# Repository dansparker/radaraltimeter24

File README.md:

# radaraltimeter24

FMCW-Radar-Höhenmesser (Radar Altimeter) für Flugzeuge mit 24-GHz-Radarmodul
(**RFbeam K-LC1a** oder **InnoSenT IVS-465**) und **STM32F405RGT6** (Rev. A) bzw.
**STM32F446** auf dem WeAct-Core-Board (Rev. B, [Schaltplan](hardware/rev_b_f446/README.md)).
Ausgabe ~61 Hz über **UART** und **CAN**. Kurze Dreieckrampen (1,17 ms), viele Rampen
gemittelt und die **Vorderkante** des Bodenechos ausgewertet: Der Boden ist aus dem Flugzeug
kein Punktziel, sondern wegen Keule und Fluggeschwindigkeit ein breiter Hügel im Spektrum.

Reichweite mit dem K-LC1a im Simulator (Empfindlichkeit nach Datenblatt, 30 m/s): über Wiese
bis etwa 100 m, über Asphalt/Wasser bis 250 m, kleinste Höhe etwa 4 m. Einzelheiten:
[hardware/rev_b_f446/README.md](hardware/rev_b_f446/README.md#mögliche-reichweite).

## Aufbau

```
lib/rdsp/            portable Radar-DSP-Bibliothek (C99, ohne malloc, wiederverwendbar)
firmware/app/        Höhenmesser-Pipeline, Konfiguration, Protokolle (hardwareunabhängig)
firmware/bsp/        STM32F405 (Rev. A) / F446 (Rev. B): Startup, Takt, Frontend (DAC/ADC/DMA), UART, CAN, Flash, IWDG
firmware/src/        main.c, Kommandozeile
test/                Radar-Simulator mit Bodenmodell + Unit-/End-to-End-Tests, Reichweitenauswertung
docs/                Signalverarbeitung, Hardware, Review/Schwachstellen
hardware/rev_b_f446/ Schaltplan Rev. B (STM32F446, TLV9064), Reichweitenabschätzung
```

## Signalverarbeitung (Kurzfassung)

Dreieck-FMCW (steigende und fallende Rampe abwechselnd, je 1,17 ms; ein Messzyklus = 7 Paare):

| Schritt | Modul | Zweck |
|---|---|---|
| 0 | `rdsp_agc` | Verstärkungsregelung (4 Stufen), ignoriert einzelne Störpulse |
| 1 | `rdsp_frame` | ADC → float, Statistik, Clipping, DC-/Trendabzug |
| 2 | `rdsp_window` | Hann-Fenster über 256 Samples, Nullauffüllung |
| 3 | `rdsp_fft` | reelle FFT 512 Punkte |
| 3a | `rdsp_clutter_update` | laufender Abzug fester Echos (Leckage, Fahrwerk), kohärenzgewichtet |
| 4 | `rdsp_spectrum` | Leistungsdichte, robuste Mittelung über Rampen (τ 40–250 ms) |
| 5 | `rdsp_edge` | Vorderkante des Bodenechos (nur rückwärts schauendes Rauschfenster) |
| 6 | `rdsp_fmcw` | Auf/Ab-Kombination → dopplerfreie Entfernung + Geschwindigkeit |
| 7 | `rdsp_track` | α-β-Tracker mit Gating, Coasting, Wiederaufnahme |

Details, Begründungen und weitere Diagramme: [docs/signal_chain.md](docs/signal_chain.md).

## Bauen

Firmware (arm-none-eabi-gcc, z. B. aus STM32CubeIDE):

```bash
sh tools/fetch_cmsis.sh
```

```bash
make -C firmware              # Rev. B (STM32F446), Standard
make -C firmware BOARD=reva   # Rev. A (STM32F405)
```

Ergebnis: `firmware/build/<board>/radar_altimeter.{elf,bin,hex}`. Alternativ kann `CMSIS=<pfad>` auf
einen vorhandenen CubeIDE-`Drivers/CMSIS`-Ordner zeigen. Der Code nutzt keine HAL, nur
CMSIS-Registerdefinitionen.

Host-Tests (gcc/clang):

```bash
make -C test
```

Reichweite/Genauigkeit gegen das Bodenmodell (einige Minuten):

```bash
make -C test range
```

## Inbetriebnahme

1. Firmware flashen, UART 115200 8N1 öffnen → `$RALT`-Zeilen.
2. `module klc1a` bzw. `module ivs465`, dann `info`.
3. **Kalibrierung** (Frequenzhub der Module unbekannt!): `bg off`, Radar auf einen Reflektor
   (Winkelreflektor, Metallplatte) in bekanntem Abstand richten, `cal1 <m>`, Abstand ändern
   (≥ 2 m, besser ≥ 10 m), `cal2 <m>`, dann `bg on`, `save`.
4. Optional, eingebaut am Flugzeug: `zero 0` (Anzeige = 0 auf dem Boden), `save`.
5. Laufender Hintergrundabzug (`bg on`, Standard) entfernt im Flug feste Echos (Leckage, Radom,
   Fahrwerk). Bei Bodentests mit ruhendem Ziel `bg off`, vor dem Flug wieder `bg on`, `save`.

Alle Kommandos: `help`. Siehe [docs/hardware.md](docs/hardware.md) und die vollständige
**[Checkliste zur Inbetriebnahme](docs/inbetriebnahme.md)**.

## Ausgabe

UART (NMEA-ähnlich, XOR-Prüfsumme):

```
$RALT,<seq>,<höhe_m>,<vs_m/s>,<snr_dB>,<gain>,<status_hex>*CS
$RDBG,<seq>,<roh_m>,<kante_steigend_Hz>,<kante_fallend_Hz>,<f_R_Hz>,<track>,<tau_ms>*CS   (out 2)
```

Höhe und Geschwindigkeit sind leer, wenn ungültig. CAN (Standard-ID `0x3A0`, 500 kbit/s):

| ID | Bytes |
|---|---|
| 0x3A0 | int32 Höhe [mm], int16 Steigrate [cm/s], uint8 Status (Low-Byte), uint8 Zähler(0-3) \| Gain(4-5) \| degraded(6) \| busy(7) |
| 0x3A1 | uint16 Status, uint8 SNR [dB], uint8 Track-Zustand, uint32 seq (jede 8. Messung) |

Statusbits: `0x0001` gültig, `0x0002` Coasting, `0x0004` kein Ziel, `0x0008` Clipping,
`0x0010` Hardwarefehler, `0x0020` nicht kalibriert, `0x0040` Frame-Überlauf,
`0x0080` degradiert (nur eine Rampenrichtung oder Kante nahe DC), `0x0100` Kalibrierung läuft,
`0x0200` Gain-Wechsel, `0x0400` Taktausfall (läuft auf HSI).
Das letzte Feld von `$RDBG` ist die aktuelle Mittelungszeit in ms.

## Status / Einschränkungen

Die Firmware ist im Simulator getestet und kompiliert, **aber noch nicht auf der Hardware
erprobt**. Bekannte Grenze: Bei hoher Fluggeschwindigkeit misst sie systematisch zu niedrig
(30 m/s: ≈ 0,5 m, 60 m/s: 1–2 m). Offene Punkte und gefundene Schwachstellen: [docs/review.md](docs/review.md).
Nicht als zertifiziertes Avionik-Gerät gedacht.

## Lizenz

MIT, siehe [LICENSE](LICENSE).

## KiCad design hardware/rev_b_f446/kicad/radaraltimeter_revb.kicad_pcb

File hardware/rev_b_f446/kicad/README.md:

# KiCad-Projekt Rev. B (KiCad 9)

Inhaltlich gleich wie [`../schaltplan.svg`](../schaltplan.svg). Der SVG-Plan ist die lesbare
Zeichnung. Der KiCad-Schaltplan ist netzlistenartig aufgebaut: Jeder Pin hat ein Netzlabel,
geordnet nach den sechs Blöcken des SVG-Plans.

| Datei | Inhalt |
|---|---|
| `radaraltimeter_revb.kicad_pro / .kicad_sch / .kicad_pcb` | Projekt, Schaltplan, Platine |
| `radar_revb.kicad_sym`, `radar_revb.pretty/` | Projektbibliothek: WeAct-Board, K-LC1a, TS3A5017 (TSSOP), PESD3V3S2UT |
| `radaraltimeter_revb_schaltplan.pdf`, `_platine.pdf`, `_bestueckung.pdf` | Export zum Ansehen ohne KiCad (Bestückungsplan mit allen Referenzen) |
| `generator/` | Skripte, aus denen alles erzeugt wurde (`design.py` = Netzliste) |

## Stand

- **Schaltplan:** ERC 0 Fehler, 0 Warnungen.
- **Platine:**
  - 4 Lagen, 86 × 64 mm, 4 × M3 an GND.
  - GND-Fläche auf In1 (durchgehend) und B.Cu; jedes SMD-GND-Pad hat ein eigenes Via auf In1.
  - ZF-Kette und VCO-Ansteuerung von Hand verankert (`generator/place_if.py`): U1 um 180° gedreht,
    die Stufen 1 und 2 zeigen zum Modulpin. C21 sitzt direkt zwischen Modulpin 3 und dem U1-Eingang,
    U7 mit 1D neben U1 Pin 6. Die übrigen Teile setzt das Skript in Signalrichtung auf den nächsten
    freien Platz, Abblockkondensatoren an ihren Versorgungspin, R32/C27 an PC4.
  - Restliche Gruppen gepackt, Zweipoler per Tausch/Drehung auf kurze Netze optimiert.
  - **Mit Freerouting geroutet** (F.Cu 1,2 m, In2 0,23 m, B.Cu 0,15 m; In1 bleibt ungeteilte
    Masselage). DRC mit Schaltplan-Parität: **0 Verstöße**, 0 offene Verbindungen.
  - Analoge Netze, alle auf F.Cu über der Masselage und ohne Via: IF_RAW 8 mm, IF_AC 6 mm,
    IF_FB1 6 mm, IF1 4 mm, IF_HP 13 mm, IF_FB2 12 mm, ADC_IF 5 mm, VCO_DRV 10 mm.
    VCO_TUNE 24 mm mit einem Via. Die langen Wege tragen niederohmige Signale
    (AA1/AA2-Ausgänge, DAC, Steuerleitungen).
  - Bestückungsdruck aufgeräumt (`generator/silk.py`): Referenzen auf freien Plätzen, weg von
    Pads, Vias, anderem Druck und der Kante; bei ICs auf dem Gehäuse. Wo im dichten ZF-Feld kein
    Platz ist (21 Kleinteile, TP1, D6), steht die Referenz nur auf F.Fab, also im Bestückungsplan
    `radaraltimeter_revb_bestueckung.pdf`. Library-Footprints bleiben unverändert.
  - Vor der Bestellung trotzdem in KiCad ansehen: Leiterbahnen glätten, Kabelaustritt J1 prüfen.
- Netzklasse `Power` (0,5 mm) für VIN*, BUCK_SW, V_PRE*, 5V_* und GND.

Anordnung (oben gesehen):
- WeAct-Board links auf Buchsenleisten 2 × 2×15, um 180° gedreht. USB-C liegt an der Oberkante, die Analog-Leiste (PA4, PC4, PC5, PB0, PB1) zeigt zur Mitte.
- K-LC1a **auf der Unterseite**, Antenne nach unten. Die Pins stehen rechts, die ZF-Kette liegt darüber auf der Oberseite.
- Schaltregler und Stecker J1 liegen unten, möglichst weit weg von der ZF-Kette.

## Neu erzeugen

Änderungen an Bauteilen oder Netzen in `generator/design.py` machen, dann:

```bash
python generator/mklib.py && python generator/gen_sch.py
"D:/Program Files/KiCad/9.0/bin/python.exe" generator/gen_pcb.py
"D:/Program Files/KiCad/9.0/bin/python.exe" generator/route.py
"D:/Program Files/KiCad/9.0/bin/python.exe" generator/silk.py
```

`gen_pcb.py` und `route.py` brauchen das Python von KiCad (Modul `pcbnew`), `route.py` zusätzlich
Java und Freerouting (Pfad über `FREEROUTING`, Standard `~/AppData/Local/freerouting/freerouting-1.9.0.jar`).
Der K-LC1a hat einen eigenen Unterseiten-Footprint statt eines gespiegelten Teils, weil der
DSN-Export von KiCad 9 gespiegelten Durchsteck-Pads die Innenlagen nimmt. **Achtung:** Neu erzeugen
überschreibt die Platine samt Routing. Sobald in KiCad geroutet wird, Änderungen nur noch in
KiCad machen (Schaltplan → Platine mit F8).

## Vor dem Routing/Bestellen prüfen

1. **WeAct-Pinfolge:** Die Pinfolge stammt aus dem Board-Shape-PDF V1.0 von WeAct. Pro Leiste gilt: linke Beschriftung = äußere Reihe (links) bzw. innere Reihe (rechts).
   - Genutzt werden PA2, PA3, PA4, PC4, PC5, PB0, PB1, PB8, PB9, PB12, PB13, PC6, PC7, 5V, 3V3 und GND.
   - Mit Durchgangsprüfer am echten Board (V1.1) nachmessen, vor allem 5V/GND unten rechts und 3V3/GND unten links. Die Reihen L12 bis L14 innen sind unbeschriftet und bleiben offen.
2. **K-LC1a:**
   - Laut Datenblatt Fig. 3 sind die Pins 2,54 mm, Pin 1 sitzt 7,42 mm von der Kante.
   - Der Abstand der Pinreihe zum Modulrand (1,45 mm) ist aus der Zeichnung geschätzt.
   - Bohrung 1,0 mm für 0,64-mm-Pins. Abstand Platine zu Modul so wählen, dass nichts auf der Unterseite das Gehäuse berührt.
3. **TS3A5017 TSSOP-16:** Pinbelegung nach TI SCDS188G (1 = 1EN, 2 = IN2, 7 = 1D, 14 = IN1, 15 = 2EN, 16 = V+). Die Kanalzuordnung (S1 = 55,5-fach … S4 = 1-fach) muss zur Tabelle der Firmware passen.
4. **Footprints der Fremdteile:**
   - J1 ist JST GH, Kabelaustritt prüfen.
   - L1/L2 als Bourns SRN4018 oder Gleichwertiges (L2: Sättigungsstrom ≥ 1 A).
   - C21 ist Folie im Format 1812, eine passende Bauform suchen.
5. **Layout-Regeln** (siehe Hinweise im SVG-Plan):
   - Massefläche nicht auftrennen.
   - IF_RAW → C21 → U1A kurz halten.
   - BUCK_SW-Schleife (U3, D4, L2, C2) klein halten und weit weg von der ZF.
   - ADC_IF mit R32/C27 nahe an PC4 führen.

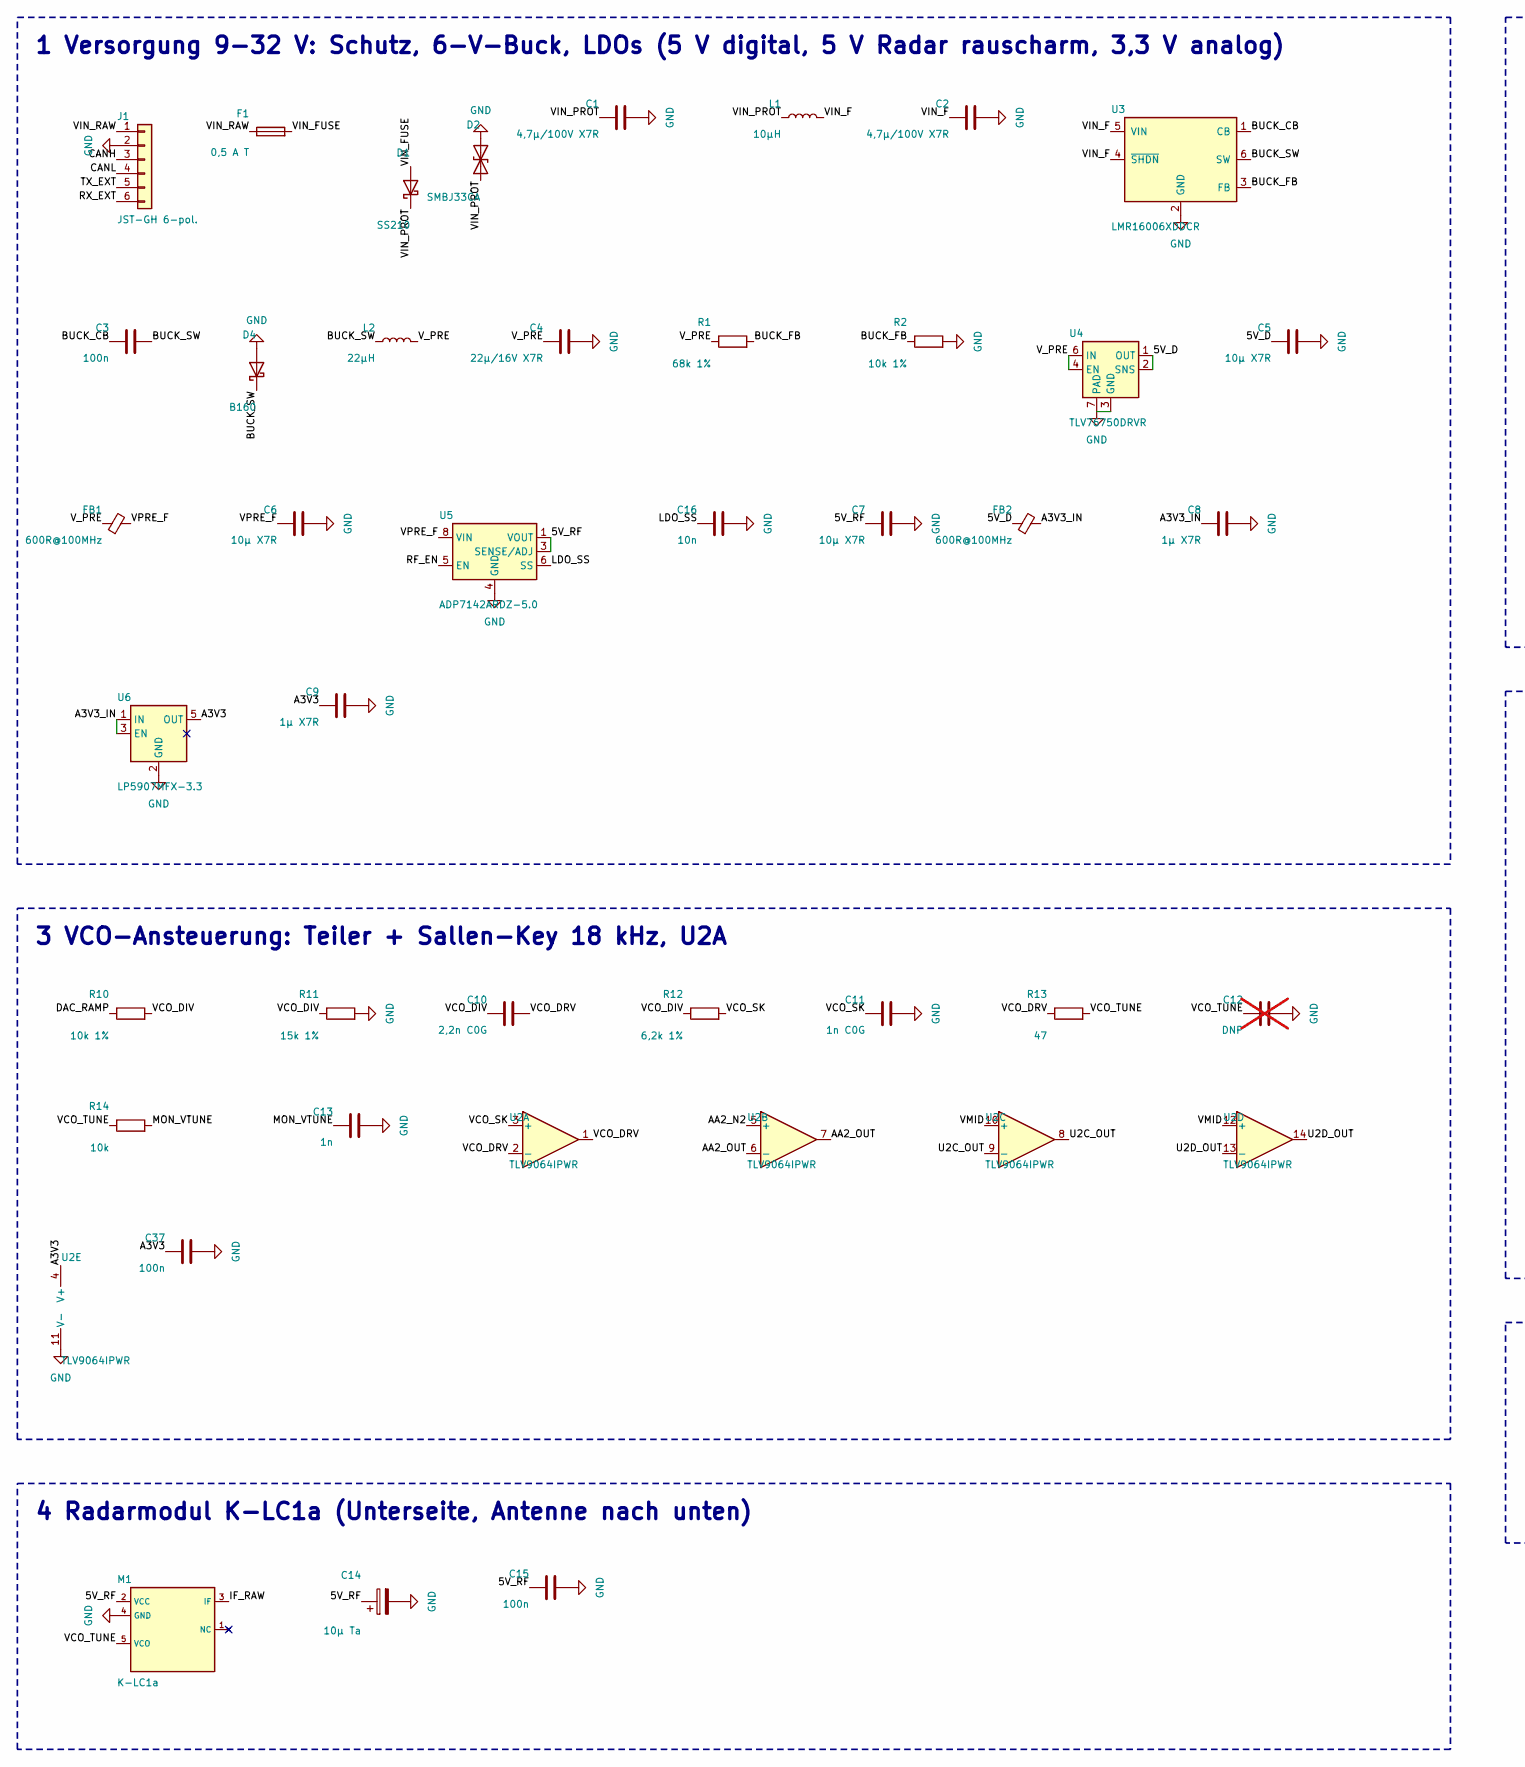
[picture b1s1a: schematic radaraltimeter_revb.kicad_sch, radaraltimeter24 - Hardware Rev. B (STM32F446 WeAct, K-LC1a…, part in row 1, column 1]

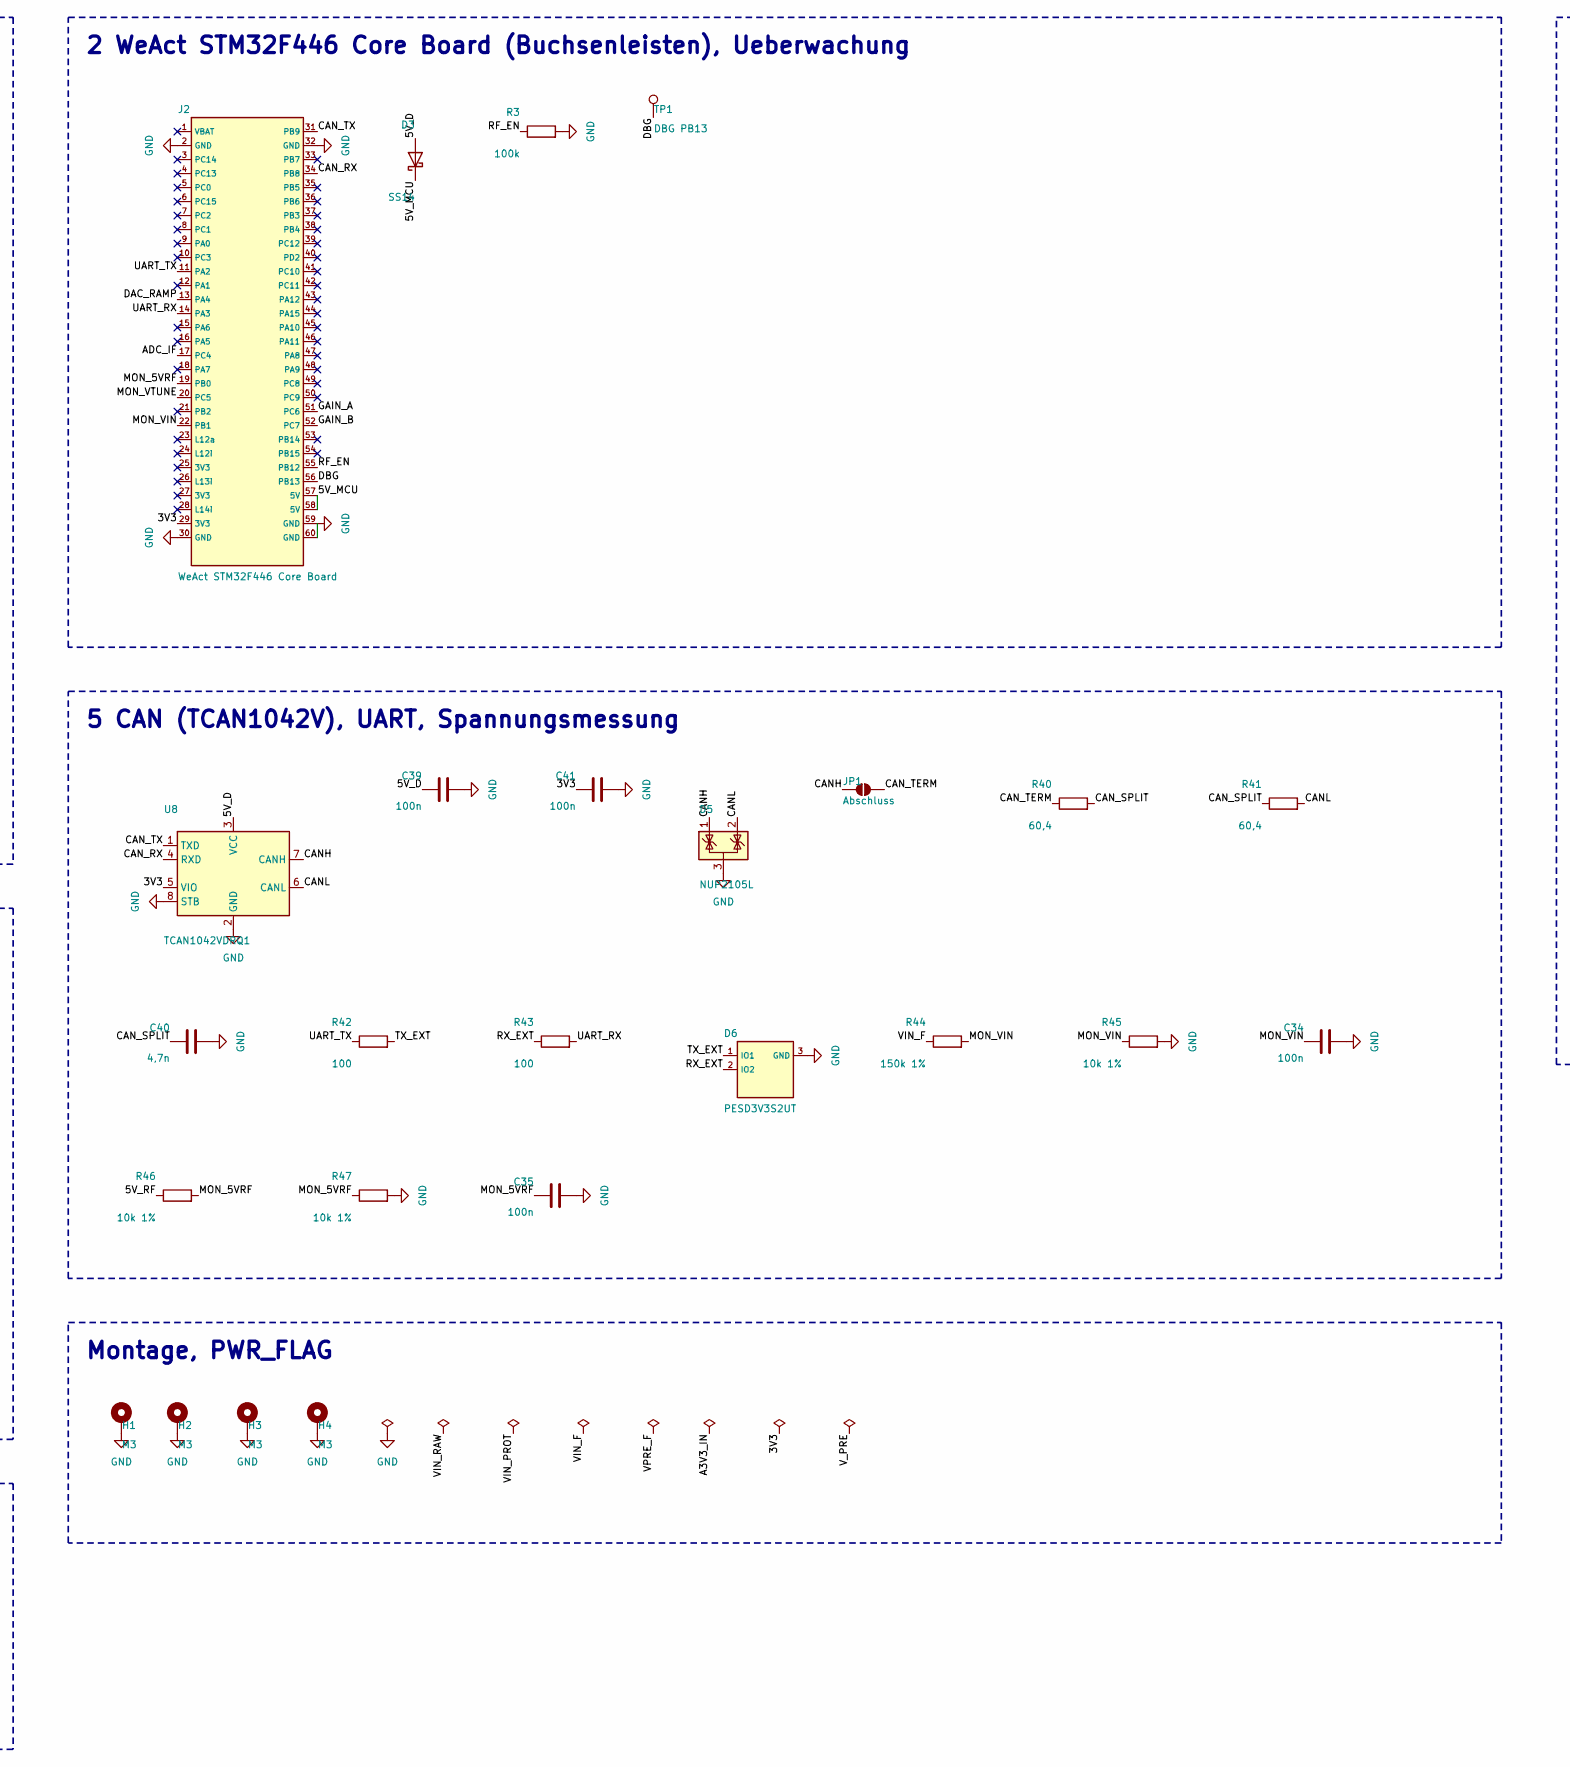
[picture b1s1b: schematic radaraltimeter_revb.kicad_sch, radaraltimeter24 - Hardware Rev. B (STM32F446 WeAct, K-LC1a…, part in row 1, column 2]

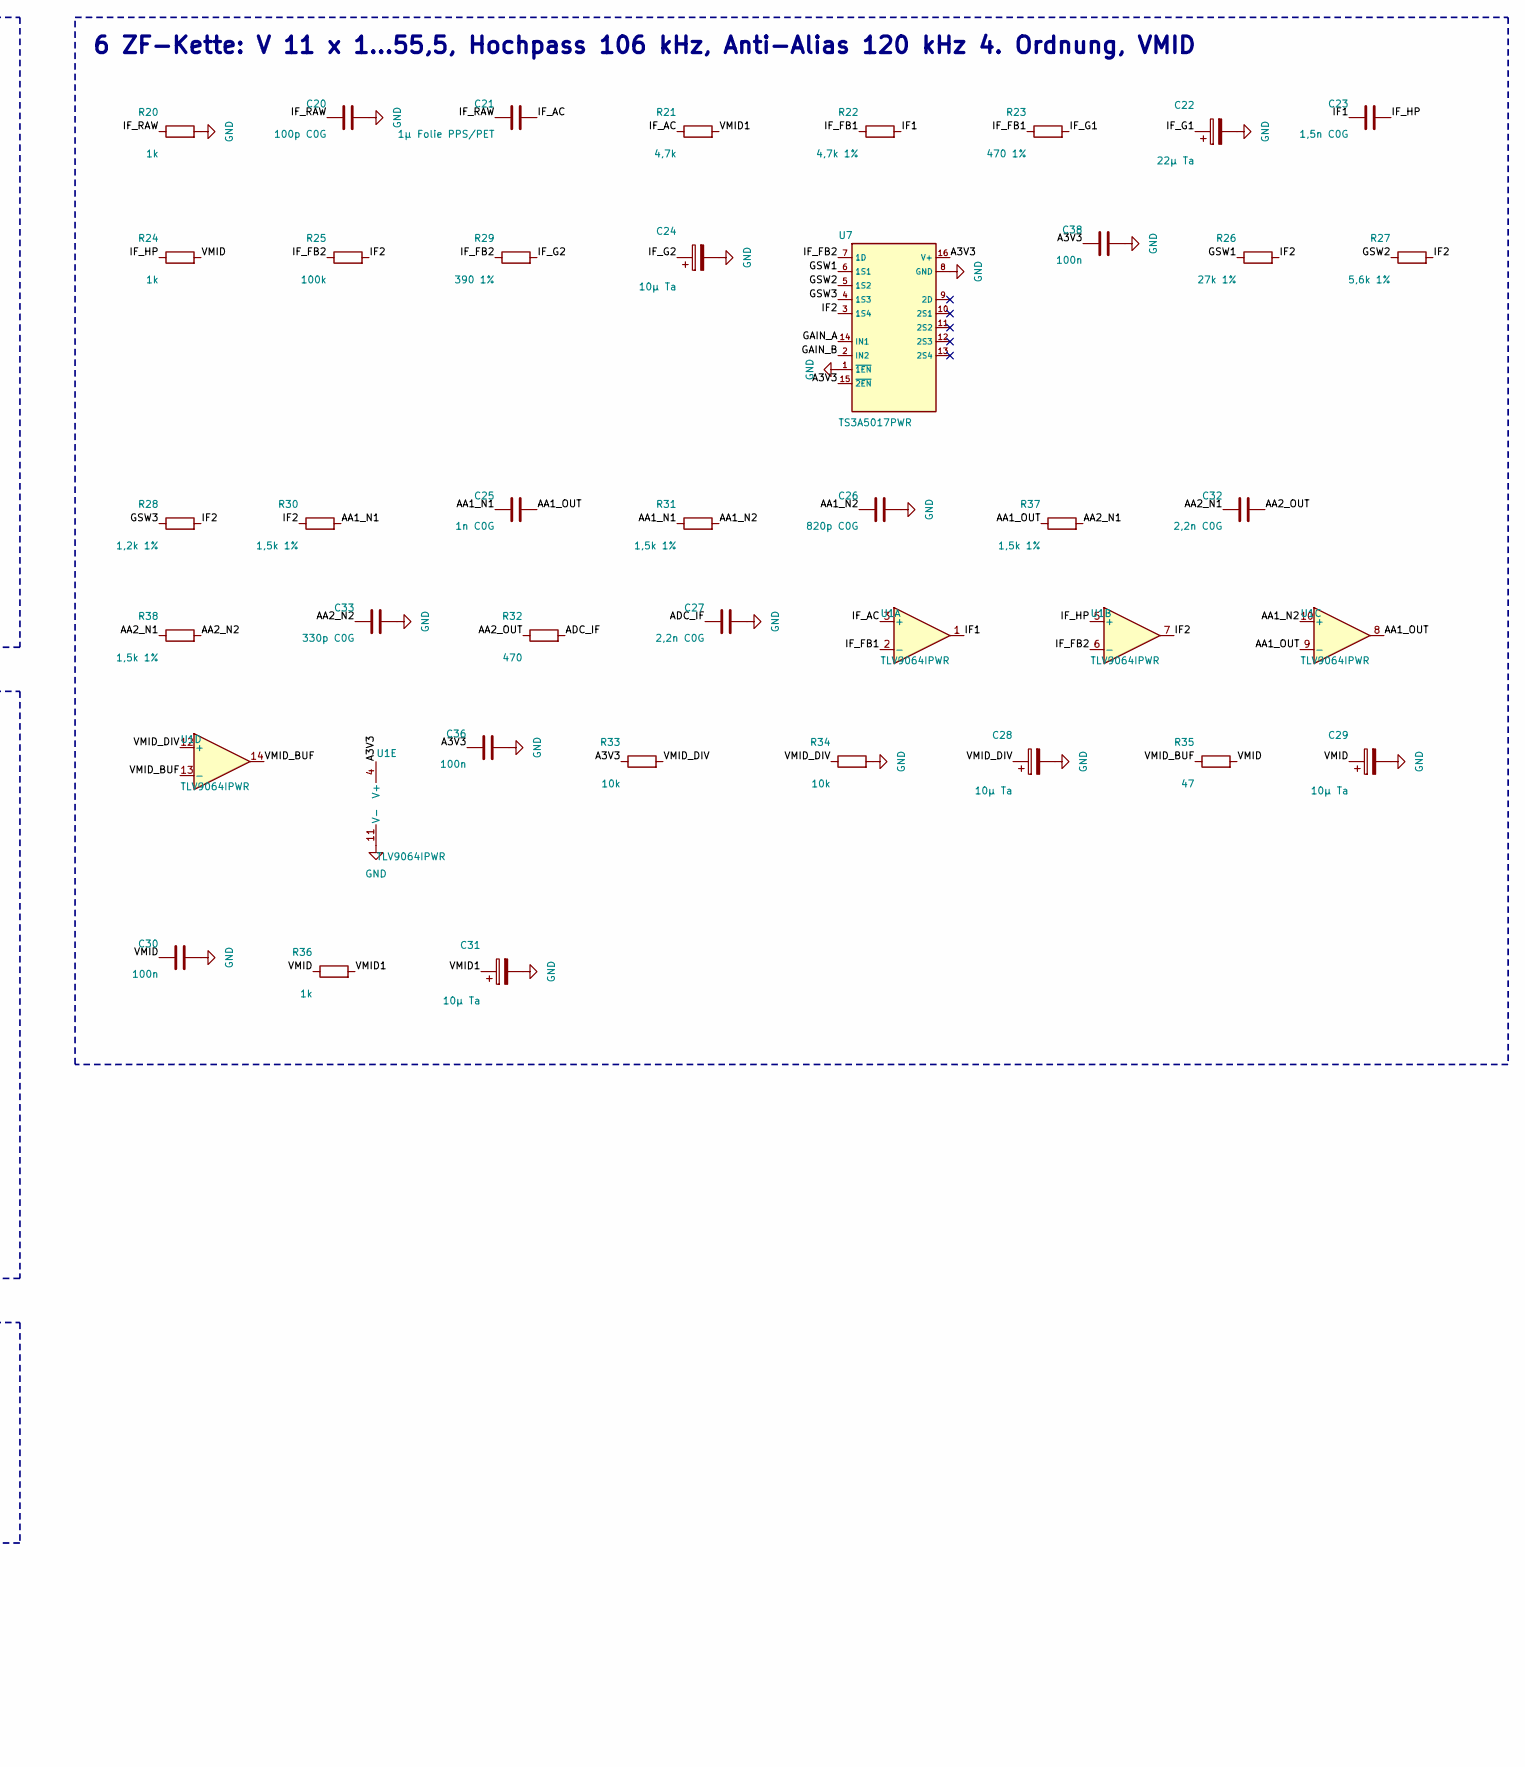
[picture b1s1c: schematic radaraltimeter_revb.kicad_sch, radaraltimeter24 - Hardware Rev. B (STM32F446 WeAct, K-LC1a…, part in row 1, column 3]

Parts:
C1, C2: 4,7µ/100V X7R; C_1210_3225Metric
C3, C15, C30, C34, C35, C36, C37, C38, C39, C41: 100n; C_0603_1608Metric
C4: 22µ/16V X7R; C_1206_3216Metric
C5, C6, C7: 10µ X7R; C_0805_2012Metric
C8, C9: 1µ X7R; C_0603_1608Metric
C10, C27, C32: 2,2n C0G; C_0603_1608Metric
C11, C25: 1n C0G; C_0603_1608Metric
C12: DNP; C_0603_1608Metric; not fitted
C13: 1n; C_0603_1608Metric
C14, C24, C28, C29, C31: 10µ Ta; CP_EIA-3528-21_Kemet-B
C16: 10n; C_0603_1608Metric
C20: 100p C0G; C_0603_1608Metric
C21: 1µ Folie PPS/PET; C_1812_4532Metric
C22: 22µ Ta; CP_EIA-3528-21_Kemet-B
C23: 1,5n C0G; C_0603_1608Metric
C26: 820p C0G; C_0603_1608Metric
C33: 330p C0G; C_0603_1608Metric
C40: 4,7n; C_0603_1608Metric
D1: SS210; D_SMA
D2: SMBJ33CA; D_SMB
D3: SS14; D_SMA
D4: B160; D_SMA
D5: NUP2105L; SOT-23
D6: PESD3V3S2UT; SOT-23
F1: 0,5 A T; Fuse_1206_3216Metric
FB1, FB2: 600R@100MHz; L_0603_1608Metric
H1, H2, H3, H4: M3; MountingHole_3.2mm_M3_Pad_Via
J1: JST-GH 6-pol.; JST_GH_SM06B-GHS-TB_1x06-1MP_P1.25mm_Horizontal
J2: WeAct STM32F446 Core Board; WeAct_STM32F4_64Pin_CoreBoard
JP1: Abschluss; SolderJumper-2_P1.3mm_Open_RoundedPad1.0x1.5mm
L1: 10µH; L_Bourns-SRN4018
L2: 22µH; L_Bourns-SRN4018
M1: K-LC1a; RFbeam_K-LC1a_Bottom
R1: 68k 1%; R_0603_1608Metric
R2, R10, R45, R46, R47: 10k 1%; R_0603_1608Metric
R3, R25: 100k; R_0603_1608Metric
R11: 15k 1%; R_0603_1608Metric
R12: 6,2k 1%; R_0603_1608Metric
R13, R35: 47; R_0603_1608Metric
R14, R33, R34: 10k; R_0603_1608Metric
R20, R24, R36: 1k; R_0603_1608Metric
R21: 4,7k; R_0603_1608Metric
R22: 4,7k 1%; R_0603_1608Metric
R23: 470 1%; R_0603_1608Metric
R26: 27k 1%; R_0603_1608Metric
R27: 5,6k 1%; R_0603_1608Metric
R28: 1,2k 1%; R_0603_1608Metric
R29: 390 1%; R_0603_1608Metric
R30, R31, R37, R38: 1,5k 1%; R_0603_1608Metric
R32: 470; R_0603_1608Metric
R40, R41: 60,4; R_0603_1608Metric
R42, R43: 100; R_0603_1608Metric
R44: 150k 1%; R_0603_1608Metric
TP1: DBG PB13; TestPoint_Pad_D1.5mm
U1, U2: TLV9064IPWR; TSSOP-14_4.4x5mm_P0.65mm
U3: LMR16006XDDCR; SOT-23-6
U4: TLV76750DRVR; WSON-6-1EP_2x2mm_P0.65mm_EP1x1.6mm
U5: ADP7142ARDZ-5.0; SOIC-8-1EP_3.9x4.9mm_P1.27mm_EP2.29x3mm
U6: LP5907MFX-3.3; SOT-23-5
U7: TS3A5017PWR; TSSOP-16_4.4x5mm_P0.65mm
U8: TCAN1042VDRQ1; SOIC-8_3.9x4.9mm_P1.27mm

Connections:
/3V3: C41.1, J2.29 (3V3), U8.5 (VIO)
/5V_D: C5.1, C39.1, D3.2 (A), FB2.1, U4.1 (OUT), U4.2 (SNS), U8.3 (VCC)
/5V_MCU: D3.1 (K), J2.57 (5V), J2.58 (5V)
/5V_RF: C7.1, C14.1, C15.1, M1.2 (VCC), R46.1, U5.1 (VOUT), U5.2 (VOUT), U5.3 (SENSE/ADJ)
/A3V3: C9.1, C36.1, C37.1, C38.1, R33.1, U1.4 (V+), U2.4 (V+), U6.5 (OUT), U7.15 (~2EN), U7.16 (V+)
/A3V3_IN: C8.1, FB2.2, U6.1 (IN), U6.3 (EN)
/AA1_N1: C25.1, R30.2, R31.1
/AA1_N2: C26.1, R31.2, U1.10 (+)
/AA1_OUT: C25.2, R37.1, U1.8, U1.9 (-)
/AA2_N1: C32.1, R37.2, R38.1
/AA2_N2: C33.1, R38.2, U2.5 (+)
/AA2_OUT: C32.2, R32.1, U2.6 (-), U2.7
/ADC_IF: C27.1, J2.17 (PC4), R32.2
/BUCK_CB: C3.1, U3.1 (CB)
/BUCK_FB: R1.2, R2.1, U3.3 (FB)
/BUCK_SW: C3.2, D4.1 (K), L2.1, U3.6 (SW)
/CANH: D5.1 (K), J1.3, JP1.1 (A), U8.7 (CANH)
/CANL: D5.2 (K), J1.4, R41.2, U8.6 (CANL)
/CAN_RX: J2.34 (PB8), U8.4 (RXD)
/CAN_SPLIT: C40.1, R40.2, R41.1
/CAN_TERM: JP1.2 (B), R40.1
/CAN_TX: J2.31 (PB9), U8.1 (TXD)
/DAC_RAMP: J2.13 (PA4), R10.1
/DBG: J2.56 (PB13), TP1.1
/GAIN_A: J2.51 (PC6), U7.14 (IN1)
/GAIN_B: J2.52 (PC7), U7.2 (IN2)
/GSW1: R26.1, U7.6 (1S1)
/GSW2: R27.1, U7.5 (1S2)
/GSW3: R28.1, U7.4 (1S3)
/IF1: C23.1, R22.2, U1.1
/IF2: R25.2, R26.2, R27.2, R28.2, R30.1, U1.7, U7.3 (1S4)
/IF_AC: C21.2, R21.1, U1.3 (+)
/IF_FB1: R22.1, R23.1, U1.2 (-)
/IF_FB2: R25.1, R29.1, U1.6 (-), U7.7 (1D)
/IF_G1: C22.1, R23.2
/IF_G2: C24.1, R29.2
/IF_HP: C23.2, R24.1, U1.5 (+)
/IF_RAW: C20.1, C21.1, M1.3 (IF), R20.1
/LDO_SS: C16.1, U5.6 (SS)
/MON_5VRF: C35.1, J2.19 (PB0), R46.2, R47.1
/MON_VIN: C34.1, J2.22 (PB1), R44.2, R45.1
/MON_VTUNE: C13.1, J2.20 (PC5), R14.2
/RF_EN: J2.55 (PB12), R3.1, U5.5 (EN)
/RX_EXT: D6.2 (IO2), J1.6, R43.1
/TX_EXT: D6.1 (IO1), J1.5, R42.2
/U2C_OUT: U2.8, U2.9 (-)
/U2D_OUT: U2.13 (-), U2.14
/UART_RX: J2.14 (PA3), R43.2
/UART_TX: J2.11 (PA2), R42.1
/VCO_DIV: C10.1, R10.2, R11.1, R12.1
/VCO_DRV: C10.2, R13.1, U2.1, U2.2 (-)
/VCO_SK: C11.1, R12.2, U2.3 (+)
/VCO_TUNE: C12.1, M1.5 (VCO), R13.2, R14.1
/VIN_F: C2.1, L1.2, R44.1, U3.4 (~SHDN), U3.5 (VIN)
/VIN_FUSE: D1.2 (A), F1.2
/VIN_PROT: C1.1, D1.1 (K), D2.1 (A1), L1.1
/VIN_RAW: F1.1, J1.1
/VMID: C29.1, C30.1, R24.2, R35.2, R36.1, U2.10 (+), U2.12 (+)
/VMID1: C31.1, R21.2, R36.2
/VMID_BUF: R35.1, U1.13 (-), U1.14
/VMID_DIV: C28.1, R33.2, R34.1, U1.12 (+)
/VPRE_F: C6.1, FB1.2, U5.7 (VIN), U5.8 (VIN)
/V_PRE: C4.1, FB1.1, L2.2, R1.1, U4.4 (EN), U4.6 (IN)
GND: C1.2, C2.2, C4.2, C5.2, C6.2, C7.2, C8.2, C9.2, C11.2, C12.2, C13.2, C14.2, C15.2, C16.2, C20.2, C22.2, C24.2, C26.2, C27.2, C28.2, C29.2, C30.2, C31.2, C33.2, C34.2, C35.2, C36.2, C37.2, C38.2, C39.2, C40.2, C41.2, D2.2 (A2), D4.2 (A), D5.3 (A), D6.3 (GND), H1.1, H2.1, H3.1, H4.1, J1.2, J2.2 (GND), J2.30 (GND), J2.32 (GND), J2.59 (GND), J2.60 (GND), M1.4 (GND), R2.2, R3.2, R11.2, R20.2, R34.2, R45.2, R47.2, U1.11 (V-), U2.11 (V-), U3.2 (GND), U4.3 (GND), U4.5 (GND), U4.7 (PAD), U5.4 (GND), U5.9 (GND), U6.2 (GND), U7.1 (~1EN), U7.8 (GND), U8.2 (GND), U8.8 (STB)

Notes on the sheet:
1 Versorgung 9-32 V: Schutz, 6-V-Buck, LDOs (5 V digital, 5 V Radar rauscharm, 3,3 V analog)
3 VCO-Ansteuerung: Teiler + Sallen-Key 18 kHz, U2A
4 Radarmodul K-LC1a (Unterseite, Antenne nach unten)
2 WeAct STM32F446 Core Board (Buchsenleisten), Ueberwachung
5 CAN (TCAN1042V), UART, Spannungsmessung
Montage, PWR_FLAG
6 ZF-Kette: V 11 x 1...55,5, Hochpass 106 kHz, Anti-Alias 120 kHz 4. Ordnung, VMID

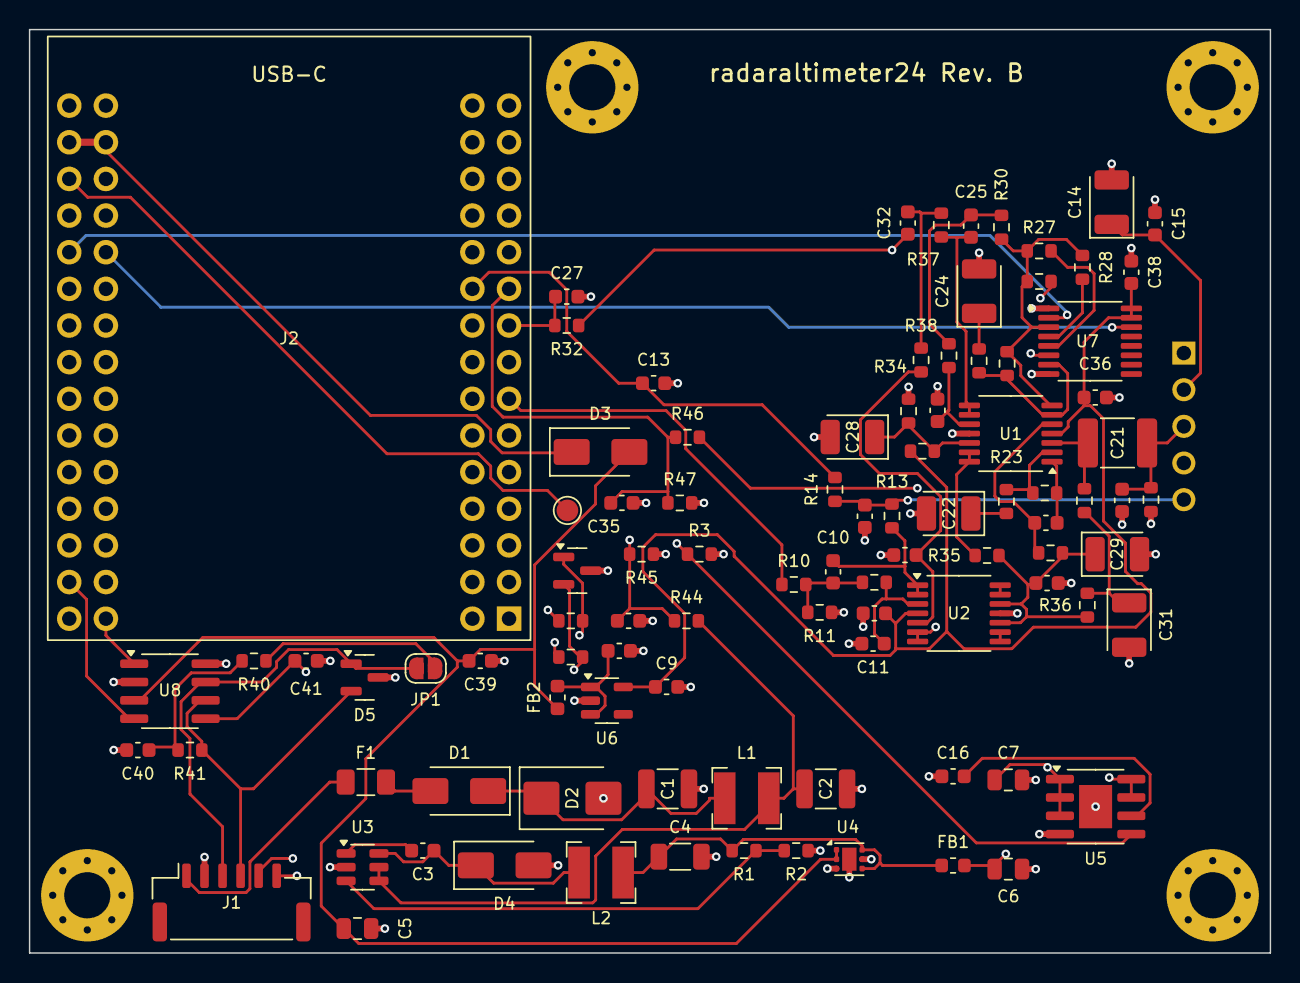
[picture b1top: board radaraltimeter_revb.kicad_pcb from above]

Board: 4 copper layers, 86.0 x 64.0 mm, 101 parts (0 on the bottom side), 64 nets.

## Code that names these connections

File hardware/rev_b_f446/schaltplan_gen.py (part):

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FRAME(1130, 40, 760, 385, '2  Mikrocontroller')
a('<rect class="ic" x="1380" y="70" width="220" height="340" rx="4"/>')
txt(1490, 88, 'WeAct STM32F446 Core Board', 'r', 'middle'); txt(1490, 101, 'STM32F446RET6, 168 MHz', 'v', 'middle')
left = [('5V', 120), ('GND', 150), ('3V3', 180), ('PA4  DAC1', 210), ('PC4  ADC1_IN14', 240), ('PC5  ADC1_IN15', 270), ('PB0  ADC1_IN8', 300), ('PB1  ADC1_IN9', 330)]
for nm, y in left: PIN(1365, y, nm, 'l')
right = [('PC6', 120), ('PC7', 150), ('PB9  CAN1_TX', 180), ('PB8  CAN1_RX', 210), ('PA2  USART2_TX', 240), ('PA3  USART2_RX', 270), ('PB12', 320)]
for nm, y in right: PIN(1615, y, nm, 'r')
for i, s in enumerate(['auf dem Board: USB-C (PA11/12), SWD,', 'HSE 8 MHz, LED PB2, Taster PC13,', 'µSD (PC8–12, PD2) → nicht belegen']):
    txt(1490, 358 + i * 13, s, 'v', 'middle')
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FRAME(1130, 440, 760, 355, '5  Schnittstellen und Überwachung')
BOX(1290, 505, 160, 120, 'U8 TCAN1042V', '')
PIN(1275, 525, 'TXD', 'l'); PIN(1275, 555, 'RXD', 'l'); PIN(1275, 585, 'STB', 'l')
PIN(1465, 525, 'CANH', 'r'); PIN(1465, 585, 'CANL', 'r')
PIN(1335, 490, 'VCC', 't'); PIN(1385, 490, 'VIO', 't'); PIN(1360, 640, 'GND', 'b')
S(1335, 490, '5V_D'); S(1385, 490, '3V3'); G(1360, 640)
N(1260, 525, 'CAN_TX', 'l'); wire((1260, 525), (1275, 525)); N(1260, 555, 'CAN_RX', 'l'); wire((1260, 555), (1275, 555))
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      '2  Kondensatoren im Signalpfad nur C0G, Folie oder Tantal (X7R/X5R sind piezoelektrisch → Vibration wird zu Störsignal).',
      '3  U_tune hart auf 0,12–1,86 V begrenzt; Rampe per Kalibrierung im ISM-Band 24,05–24,25 GHz halten (Mittenfrequenz ±75 MHz).',
      '4  Core-Board über D3 versorgt; vor gleichzeitigem USB-Betrieb prüfen, ob das Board eine VBUS-Diode hat (sonst Rückspeisung in den PC).',
      '5  Firmware: make -C firmware (BOARD=revb): CAN1 PB8/PB9, USART2 PA2/PA3, Gain PC6/PC7, RF_EN PB12, Config Sektor 7.']
for i, s in enumerate(hs): txt(30, 1410 + i * 16, s, 'note')
a('<rect class="ic" x="1330" y="1370" width="560" height="115" rx="6"/>')
txt(1345, 1395, 'radaraltimeter24 – Hardware Rev. B', 'big')
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
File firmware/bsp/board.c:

/**
 * @file board.c
 * @brief GPIO setup, gain switch, LEDs, debug pin, radar supply (see bsp.h).
 */
#include "bsp.h"

#if defined(BOARD_REVB)
#define GAIN_PORT   GPIOC
#define GAIN_A      6u      /* TS3A5017 IN1 */
#define GAIN_B      7u      /* TS3A5017 IN2 */
#define LED_PORT    GPIOB
#define LED_VALID   2u      /* WeAct board LED (check polarity on the board) */
#define DBG_PORT    GPIOB
#define DBG_PIN     13u
#define RF_EN_PORT  GPIOB
#define RF_EN_PIN   12u
#else
#define GAIN_PORT   GPIOB
#define GAIN_A      0u
#define GAIN_B      1u
#define LED_PORT    GPIOC
#define LED_VALID   14u     /* LED2 */
#define LED_HEART   15u     /* LED1 */
#define DBG_PORT    GPIOC
#define DBG_PIN     13u     /* FCT2 */
#endif

void gpio_cfg(GPIO_TypeDef *g, uint32_t pin, uint32_t mode, uint32_t pupd, uint32_t af)
{
    g->MODER = (g->MODER & ~(3u << (2u * pin))) | (mode << (2u * pin));
    g->PUPDR = (g->PUPDR & ~(3u << (2u * pin))) | (pupd << (2u * pin));
    g->OSPEEDR = (g->OSPEEDR & ~(3u << (2u * pin))) | (2u << (2u * pin));
    g->OTYPER &= ~(1u << pin);
    if (pin < 8u) {
        g->AFR[0] = (g->AFR[0] & ~(0xFu << (4u * pin))) | (af << (4u * pin));
    } else {
        g->AFR[1] = (g->AFR[1] & ~(0xFu << (4u * (pin - 8u)))) | (af << (4u * (pin - 8u)));
    }
}

void board_init(void)
{
    RCC->AHB1ENR |= RCC_AHB1ENR_GPIOAEN | RCC_AHB1ENR_GPIOBEN | RCC_AHB1ENR_GPIOCEN |
                    RCC_AHB1ENR_DMA1EN | RCC_AHB1ENR_DMA2EN;
    (void)RCC->AHB1ENR;

#if defined(BOARD_REVB)
    board_rf_enable(0);                 /* module stays off until the ramp runs */
    gpio_cfg(RF_EN_PORT, RF_EN_PIN, 1u, 0u, 0u);
#endif
    gpio_cfg(GPIOA, 4u, 3u, 0u, 0u);    /* DAC analog */
    gpio_cfg(GPIOC, 4u, 3u, 0u, 0u);    /* ADC analog */
    board_set_gain(0u);                 /* lowest gain before enabling outputs */
    gpio_cfg(GAIN_PORT, GAIN_A, 1u, 0u, 0u);
    gpio_cfg(GAIN_PORT, GAIN_B, 1u, 0u, 0u);
    gpio_cfg(LED_PORT, LED_VALID, 1u, 0u, 0u);
    gpio_cfg(DBG_PORT, DBG_PIN, 1u, 0u, 0u);
#if defined(BOARD_REVA)
    gpio_cfg(LED_PORT, LED_HEART, 1u, 0u, 0u);
    gpio_cfg(GPIOB, 12u, 0u, 1u, 0u);   /* FCT1 input pull-up */
#endif
}

/* Level -> A / B, one BSRR write = glitch free:
 * 0: A=1 B=1, 1: A=0 B=1, 2: A=1 B=0, 3: A=0 B=0.
 * Rev A: CD4052 via inverting BC847 (as in the legacy firmware).
 * Rev B: TS3A5017 IN1 = A, IN2 = B: 11 -> S4 (x1), 10 -> S3 (x4.04),
 *        01 -> S2 (x14.6), 00 -> S1 (x55.5) - the same level order. */
void board_set_gain(uint8_t level)
{
    static const uint32_t bsrr[4] = {
        (1u << GAIN_A) | (1u << GAIN_B),
        (1u << (GAIN_A + 16u)) | (1u << GAIN_B),
        (1u << GAIN_A) | (1u << (GAIN_B + 16u)),
        (1u << (GAIN_A + 16u)) | (1u << (GAIN_B + 16u)),
    };
    GAIN_PORT->BSRR = bsrr[level & 3u];
}

void board_led_valid(int on)
{
    LED_PORT->BSRR = on ? (1u << LED_VALID) : (1u << (LED_VALID + 16u));
}

void board_led_toggle(void)
{
#if defined(BOARD_REVA)
    LED_PORT->ODR ^= (1u << LED_HEART);
#endif
}

void board_dbg(int on)
{
    DBG_PORT->BSRR = on ? (1u << DBG_PIN) : (1u << (DBG_PIN + 16u));
}

void board_rf_enable(int on)
{
#if defined(BOARD_REVB)
    RF_EN_PORT->BSRR = on ? (1u << RF_EN_PIN) : (1u << (RF_EN_PIN + 16u));
#else
    (void)on;
#endif
}

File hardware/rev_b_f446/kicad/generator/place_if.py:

"""Platzierung der ZF-Kette und der VCO-Ansteuerung.
Feste Anker von Hand (U1, C21), danach jedes Bauteil in Signalrichtung auf den freien Platz mit der
kleinsten gewichteten Netzausdehnung; Abblockkondensatoren an ihren Versorgungspin.
Koordinaten in mm ab Platinenecke oben links (oben gesehen).
"""
import math
import pcbnew as P

# Modul-Pins (M1, Unterseite): x 80, Pin 1..5 bei y 22.42 + 2.54*(n-1); Pin 3 = IF_RAW bei y 27.50
HAND = {
    'U1': (68.0, 28.0, 180),     # Pins 1-7 (Stufe 1 und 2) rechts zum Modul, 8-14 (Anti-Alias, VMID) links
    'C21': (75.4, 28.65, 180),   # Pad 1 (IF_RAW) zum Modulpin 3, Pad 2 (IF_AC) auf gleicher Hoehe wie U1 Pin 3
    'U7': (73.5, 21.6, 0),       # Pin 7 (1D = IF_FB2) direkt neben U1 Pin 6
}
ORDER = ['R20', 'C20', 'R21', 'R22', 'R23', 'C22', 'C36', 'C23', 'R24', 'R25', 'R29', 'C24', 'C38',
         'R26', 'R27', 'R28', 'R30', 'C25', 'R31', 'C26', 'R33', 'R34', 'C28', 'R35', 'C29', 'C30', 'R36', 'C31',
         'U2', 'C37', 'R37', 'C32', 'R38', 'C33', 'R32', 'C27',
         'R13', 'C12', 'R14', 'C13', 'R12', 'C11', 'C10', 'R10', 'R11',
         'C15', 'C14', 'FB2', 'U6', 'C8', 'C9']
ANCHOR = {'C36': ('U1', '4'), 'C37': ('U2', '4'), 'C38': ('U7', '16'), 'C15': ('M1', '2'), 'C14': ('M1', '2'),
          'C9': ('U6', '5'), 'C8': ('U6', '1'), 'R32': ('J2', '17'), 'C27': ('J2', '17')}
WEIGHT = {'GND': 0.0, '/A3V3': 0.2, '/VMID': 0.6, '/GAIN_A': 0.1, '/GAIN_B': 0.1, '/MON_VTUNE': 0.2,
          '/DAC_RAMP': 0.3, '/5V_D': 0.1, '/A3V3_IN': 0.5, '/AA2_OUT': 0.3, '/VCO_TUNE': 0.6}
REGION = (35.6, 5.6, 79.0, 50.6)
MARGIN = 0.35


def run(FPS, V, OX, OY):
    mm, tomm = P.FromMM, P.ToMM
    # Rotation -> Huellrechteck und Pad-Offsets je Bauteil (relativ zur Position)
    geo = {}

    def shape(ref, rot):
        k = (ref, rot)
        if k not in geo:
            fp = FPS[ref][0]
            fp.SetOrientationDegrees(rot); fp.SetPosition(V(0, 0))
            bb = fp.GetBoundingBox(False)
            box = (tomm(bb.GetLeft()) - OX, tomm(bb.GetTop()) - OY, tomm(bb.GetRight()) - OX, tomm(bb.GetBottom()) - OY)
            pads = [(pd.GetNumber(), pd.GetNetname(), tomm(pd.GetPosition().x) - OX, tomm(pd.GetPosition().y) - OY)
                    for pd in fp.Pads()]
            geo[k] = (box, pads)
        return geo[k]

    movable = set(HAND) | set(ORDER)
    # Hindernisse: alle anderen Teile (M1 nur mit Pads, Koerper liegt unten)
    obst = []
    pads_at = {}
    for ref, (fp, c) in FPS.items():
        if ref in movable:
            continue
        if ref == 'M1':
            for pd in fp.Pads():
                b = pd.GetBoundingBox()
                obst.append((tomm(b.GetLeft()) - OX, tomm(b.GetTop()) - OY, tomm(b.GetRight()) - OX, tomm(b.GetBottom()) - OY))
        else:
            b = fp.GetBoundingBox(False)
            obst.append((tomm(b.GetLeft()) - OX, tomm(b.GetTop()) - OY, tomm(b.GetRight()) - OX, tomm(b.GetBottom()) - OY))
        for pd in fp.Pads():
            pads_at[(ref, pd.GetNumber())] = (tomm(pd.GetPosition().x) - OX, tomm(pd.GetPosition().y) - OY, pd.GetNetname())
    nb = {}                                    # Netz -> [xmin, ymin, xmax, ymax] der platzierten Pads

    def addpads(ref, pads, x, y):
        for (num, n, dx, dy) in pads:
            pads_at[(ref, num)] = (x + dx, y + dy, n)
    for (x, y, n) in list(pads_at.values()):
        if n and not n.startswith('unconnected'):
            b = nb.setdefault(n, [x, y, x, y])
            b[0], b[1], b[2], b[3] = min(b[0], x), min(b[1], y), max(b[2], x), max(b[3], y)

    def commit(ref, x, y, rot):
        box, pads = shape(ref, rot)
        fp = FPS[ref][0]
        fp.SetOrientationDegrees(rot); fp.SetPosition(V(x, y))
        obst.append((box[0] + x, box[1] + y, box[2] + x, box[3] + y))
        addpads(ref, pads, x, y)
        for (num, n, dx, dy) in pads:
            if n and not n.startswith('unconnected'):
                px, py = x + dx, y + dy
                b = nb.setdefault(n, [px, py, px, py])
                b[0], b[1], b[2], b[3] = min(b[0], px), min(b[1], py), max(b[2], px), max(b[3], py)

    def free(bx):
        if bx[0] < REGION[0] or bx[1] < REGION[1] or bx[2] > REGION[2] or bx[3] > REGION[3]:
            return False
        for o in obst:
            if not (bx[2] + MARGIN <= o[0] or o[2] + MARGIN <= bx[0] or bx[3] + MARGIN <= o[1] or o[3] + MARGIN <= bx[1]):
                return False
        return True

    for ref, (x, y, r) in HAND.items():
        commit(ref, x, y, r)

    for ref in ORDER:
        # Ziel: Schwerpunkt der schon platzierten, verbundenen Pads
        _, pads0 = shape(ref, 0)
        pts = []
        for (num, n, dx, dy) in pads0:
            if n in nb and WEIGHT.get(n, 1.0) > 0:
                b = nb[n]; pts.append(((b[0] + b[2]) / 2, (b[1] + b[3]) / 2))
        anc = ANCHOR.get(ref)
        if anc:
            ax, ay, _ = pads_at[anc]; pts = [(ax, ay)]
        tx = sum(p[0] for p in pts) / len(pts) if pts else 60.0
        ty = sum(p[1] for p in pts) / len(pts) if pts else 28.0
        best = None
        for rot in (0, 90, 180, 270):
            box, pads = shape(ref, rot)
            for i in range(-36, 37):
                for j in range(-36, 37):
                    x, y = tx + i * 0.5, ty + j * 0.5
                    if math.hypot(i, j) > 36:
                        continue
                    bx = (box[0] + x, box[1] + y, box[2] + x, box[3] + y)
                    cost = 0.0
                    for (num, n, dx, dy) in pads:
                        if not n or n.startswith('unconnected'):
                            continue
                        w = WEIGHT.get(n, 1.0)
                        px, py = x + dx, y + dy
                        if anc and n != 'GND' and (anc[0], anc[1]) in pads_at and pads_at[anc][2] == n:
                            cost += 4.0 * math.hypot(px - pads_at[anc][0], py - pads_at[anc][1])
                        if w == 0 or n not in nb:
                            continue
                        b = nb[n]
                        cost += w * ((max(b[2], px) - min(b[0], px) + max(b[3], py) - min(b[1], py))
                                     - (b[2] - b[0] + b[3] - b[1]))
                    cost += 0.02 * math.hypot(x - tx, y - ty)
                    if best and cost >= best[0]:
                        continue
                    if free(bx):
                        best = (cost, x, y, rot)
        if not best:
            raise RuntimeError('kein Platz fuer ' + ref)
        commit(ref, round(best[1], 2), round(best[2], 2), best[3])
    print('ZF/VCO von Hand platziert:', len(HAND) + len(ORDER), 'Teile')

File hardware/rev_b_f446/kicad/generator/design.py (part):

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    {str(i): J2.get(str(i)) for i in range(1, 61)}, B, 'J2')
add('D3', 'Diode', 'SS14', 'SS14', FP['SMA'], {'1': '5V_MCU', '2': '5V_D'}, B, 'AUX')
R('R3', '100k', 'RF_EN', 'GND', B, 'AUX')
add('TP1', 'Connector', 'TestPoint', 'DBG PB13', 'TestPoint:TestPoint_Pad_D1.5mm', {'1': 'DBG'}, B, 'AUX')

# ------------------------------------------------------------ 3 VCO-Ansteuerung
B = 'VCO'
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R('R32', '470', 'AA2_OUT', 'ADC_IF', B)
C('C27', '2,2n C0G', 'ADC_IF', 'GND', B)
add('U1', 'Amplifier_Operational', 'TLV9064', 'TLV9064IPWR', FP['TSSOP14'],
    {'3': 'IF_AC', '2': 'IF_FB1', '1': 'IF1',                 # A: Stufe 1, V = 11
     '5': 'IF_HP', '6': 'IF_FB2', '7': 'IF2',                 # B: Stufe 2, umschaltbar
     '10': 'AA1_N2', '9': 'AA1_OUT', '8': 'AA1_OUT',          # C: Anti-Alias Stufe 1
     '12': 'VMID_DIV', '13': 'VMID_BUF', '14': 'VMID_BUF',    # D: VMID-Puffer
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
